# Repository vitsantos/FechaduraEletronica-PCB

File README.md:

## Design da PCB do Projeto Fechadura Eletrônica
### PET - EC - UFC Sobral - 2024

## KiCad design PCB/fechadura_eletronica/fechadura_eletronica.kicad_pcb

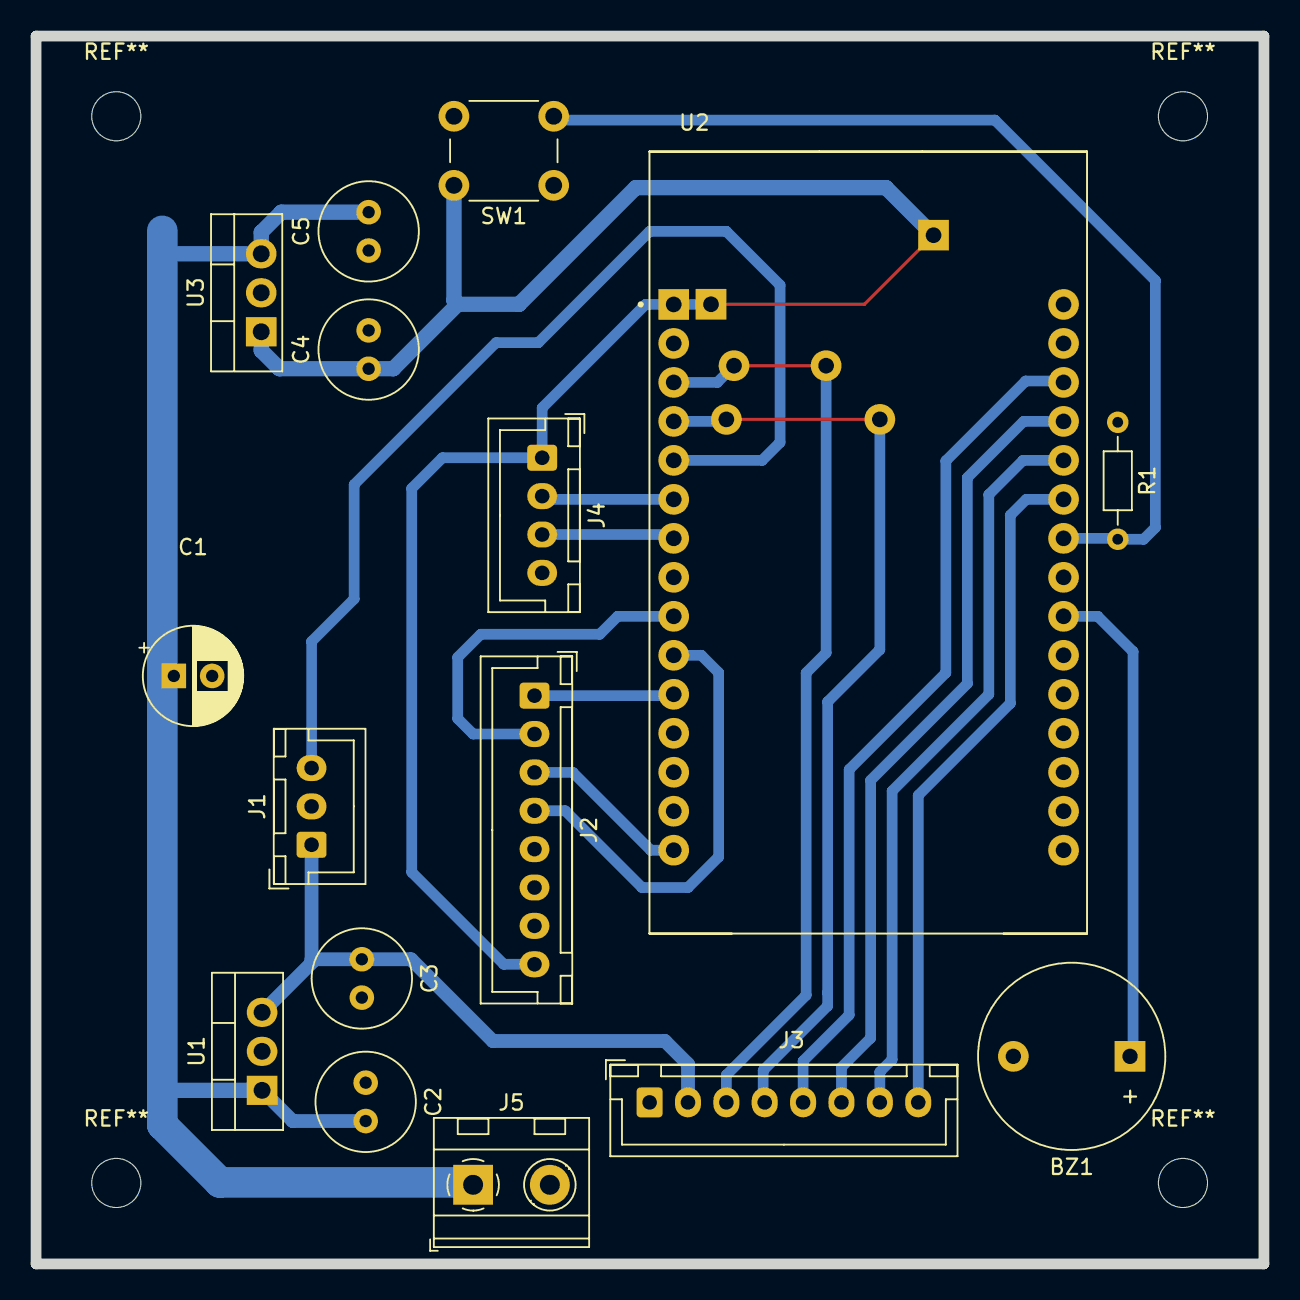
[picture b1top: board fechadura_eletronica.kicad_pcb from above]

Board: 2 copper layers, 80.0 x 80.0 mm, 16 parts (0 on the bottom side), 19 nets.

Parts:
BZ1: Buzzer; Buzzer_12x9.5RM7.6
C1: 100uF; CP_Radial_D6.3mm_P2.50mm
C2, C3, C4, C5: C; C_Radial_D6.3mm_H7.0mm_P2.50mm
J1: Relay Module; JST_XH_B3B-XH-A_1x03_P2.50mm_Vertical
J2: RFID - RC522; JST_XH_B8B-XH-A_1x08_P2.50mm_Vertical
J3: LCD 16X2; JST_XH_B8B-XH-A_1x08_P2.50mm_Vertical
J4: DY50; JST_XH_B4B-XH-A_1x04_P2.50mm_Vertical
J5: Screw_Terminal_01x02; TerminalBlock_MetzConnect_Type094_RT03502HBLU_1x02_P5.00mm_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
R1: R5.1K; R_Axial_DIN0204_L3.6mm_D1.6mm_P7.62mm_Horizontal
SW1: reset button; SW_PUSH_6mm_H4.3mm
U1: LM7805 - regulator; TO-220-3_Vertical
U2: ESP32-DEVKIT-V1; MODULE_ESP32_DEVKIT_V1
U3: LD1117S33TR_SOT223; TO-220-3_Vertical

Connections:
+3.3V: C4.1, J2.8 (3.3V), J4.1 (3.3V), SW1.1, U2.1 (3V3), U3.1 (VI)
+5V: C3.1, J1.1 (5V), J3.2 (VDD(5V)), U1.3 (VO), U2.30 (VIN)
+12V: C1.1, C2.2, C5.2, J5.1, U1.1 (VI), U3.3 (VO)
GND: BZ1.2 (-), C1.2, C2.1, C3.2, C4.2, C5.1, J1.2 (GND), J2.6 (GND), J3.1 (VSS(GND)), J4.4 (GND), J5.2, R1.1, U1.2 (GND), U2.2 (GND), U2.29 (GND), U3.2 (GND)
unnamed: BZ1.1 (+), U2.22 (D33)
unnamed: J1.3 (IN), U2.5 (D4)
unnamed: J2.4 (MISO), U2.10 (D19)
unnamed: J2.3 (MOSI), U2.15 (D23)
unnamed: J2.2 (SCK), U2.9 (D18)
unnamed: J2.1 (SDA), U2.11 (D21)
unnamed: J3.5 (D4), U2.28 (D13)
unnamed: J3.6 (D5), U2.27 (D12)
unnamed: J3.7 (D6), U2.26 (D14)
unnamed: J3.8 (D7), U2.25 (D27)
unnamed: J3.4 (E), U2.4 (D2)
unnamed: J3.3 (RS), U2.3 (D15)
unnamed: J4.3 (RX), U2.7 (TX2)
unnamed: J4.2 (TX), U2.6 (RX2)
unnamed: R1.2, SW1.2, U2.24 (D26)

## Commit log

2024-05-13 feito o roteamento das trilhas da PCB
2024-05-13 arquivos e diretorios inuteis removidos
2024-08-19 adicionado regulador 3.3v LD1117 e PCB refatorada
2024-08-21 versao final pcb
2024-08-26 versao final
2024-08-26 versão final
2024-08-26 removed-useless-files
